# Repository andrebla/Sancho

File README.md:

# Sancho
DIY macro keyboard

|  | 
| - |

Sancho is an open-source custom macro keyboard. An OLED display show keys functions in real time, and an encoder is used to change functions.
 
## PCB ##

|  | 
| - |

## Pictures ##
|  | 
| - |

|  |
| - |

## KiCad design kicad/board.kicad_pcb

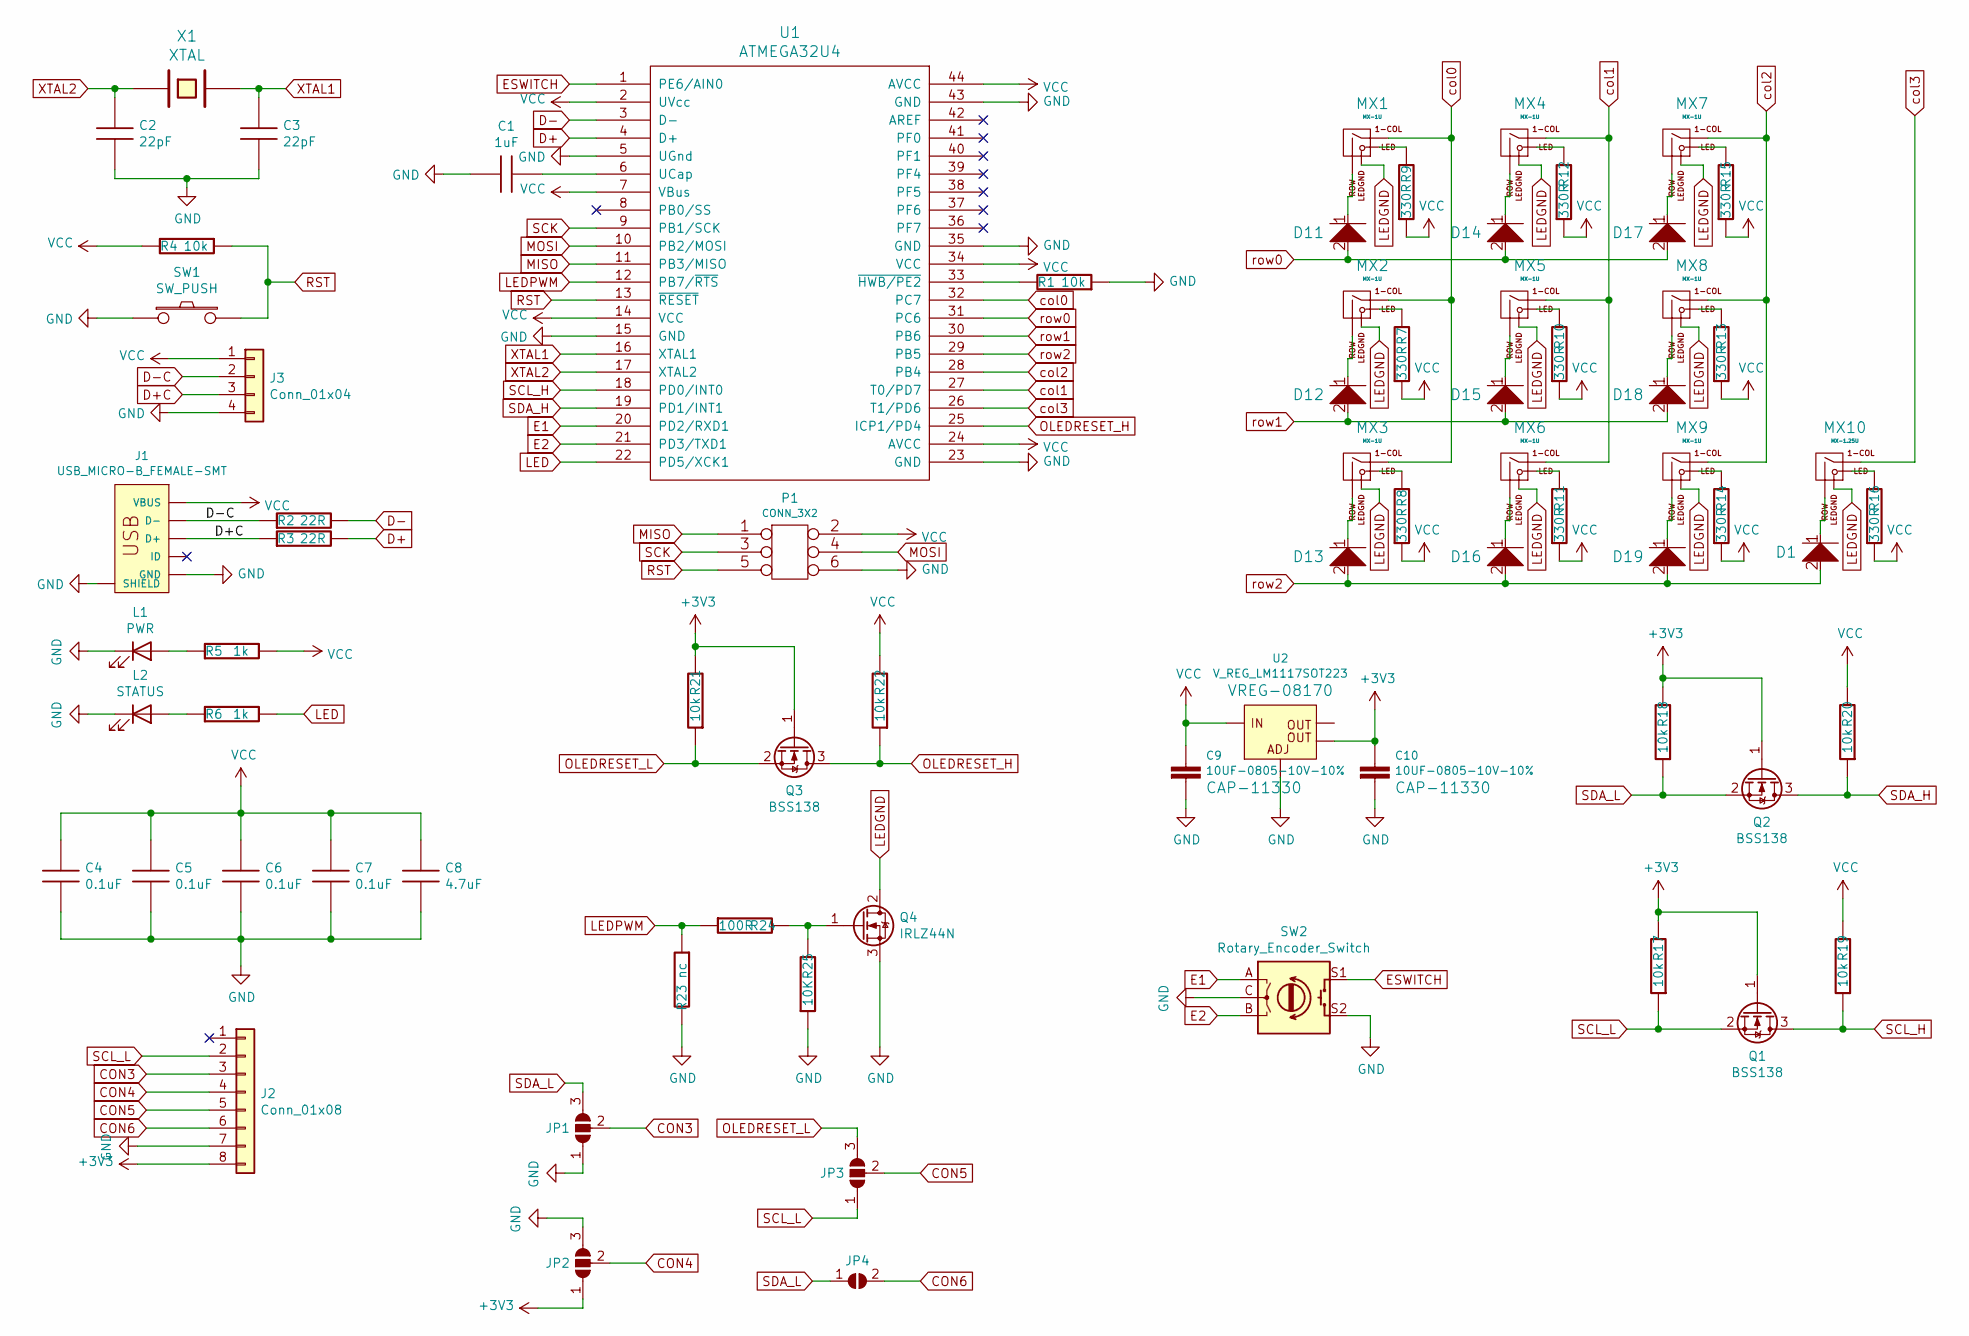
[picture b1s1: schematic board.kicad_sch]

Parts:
C1: 1uF; C_0603_1608Metric
C2, C3: 22pF; C_0603_1608Metric
C4, C5, C6, C7: 0.1uF; C_0603_1608Metric
C8: 4.7uF; C_0603_1608Metric
C9, C10: 10UF-0805-10V-10%; C_0805_2012Metric
D1, D11, D12, D13, D14, D15, D16, D17, D18, D19: D; D_SOD123_axial
J1: USB_MICRO-B_FEMALE-SMT; USB-B-MICRO-SMD
J2: Conn_01x08; PinHeader_1x08_P2.54mm_Vertical
J3: Conn_01x04; 1X04_1.27MM
JP1, JP2, JP3: SolderJumper_3_Open; SolderJumper-3_P1.3mm_Open_RoundedPad1.0x1.5mm
JP4: SolderJumper_2_Open; SolderJumper-2_P1.3mm_Open_RoundedPad1.0x1.5mm
L1: PWR; LED_0603_1608Metric
L2: STATUS; LED_0603_1608Metric
MX1, MX2, MX3, MX4, MX5, MX6, MX7, MX8, MX9: MX-1U
MX10: MX-1.25U
P1: CONN_3X2; AVR_ICSP_3x2
Q1, Q2, Q3: BSS138; SOT-23
Q4: IRLZ44N; SOT-223-3_TabPin2
R1, R4, R17, R18, R19, R20, R21, R22: 10k; R_0603_1608Metric
R2, R3: 22R; R_0603_1608Metric
R5, R6: 1k; R_0603_1608Metric
R7, R8, R9, R10, R11, R12, R13, R14, R15, R16: 330R; R_0603_1608Metric
R23: nc; R_0603_1608Metric
R24: 100R; R_0603_1608Metric
R25: 10K; R_0603_1608Metric
SW1: SW_PUSH; SW_SPST_FSMSM
SW2: Rotary_Encoder_Switch; RotaryEncoder_Alps_EC11E-Switch_Vertical_H20mm
U1: ATMEGA32U4; QFP44
U2: V_REG_LM1117SOT223; SOT223
X1: XTAL; Crystal_SMD_HC49-SD

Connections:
+3V3: C10.1, J2.8, JP2.1 (A), Q1.1 (G), Q2.1 (G), Q3.1 (G), R17.2, R18.2, R21.2, U2.4 (OUT)
CON3: J2.3, JP1.2 (C)
CON4: J2.4, JP2.2 (C)
CON5: J2.5, JP3.2 (C)
CON6: J2.6, JP4.2 (B)
D+: R3.2, U1.4 (D+)
D+C: J1.D+, J3.3, R3.1
D-: R2.2, U1.3 (D-)
D-C: J1.D-, J3.2, R2.1
E1: SW2.A, U1.20 (PD2/RXD1)
E2: SW2.B, U1.21 (PD3/TXD1)
ESWITCH: SW2.S1, U1.1 (PE6/AIN0)
GND: C1.1, C2.2, C3.2, C4.2, C5.2, C6.2, C7.2, C8.2, C9.2, C10.2, J1.GND, J1.SHIE (SHIELD), J2.7, J3.4, JP1.1 (A), JP2.3 (B), L1.1 (K), L2.1 (K), P1.6, Q4.3 (S), R1.1, R23.2, R25.1, SW1.1, SW2.C, SW2.S2, U1.5 (UGnd), U1.15 (GND), U1.23 (GND), U1.35 (GND), U1.43 (GND), U2.1 (ADJ)
LED: R6.2, U1.22 (PD5/XCK1)
LEDGND: MX1.4 (LEDGND), MX2.4 (LEDGND), MX3.4 (LEDGND), MX4.4 (LEDGND), MX5.4 (LEDGND), MX6.4 (LEDGND), MX7.4 (LEDGND), MX8.4 (LEDGND), MX9.4 (LEDGND), MX10.4 (LEDGND), Q4.2 (D)
LEDPWM: R23.1, R24.1, U1.12 (PB7/~RTS)
MISO: P1.1, U1.11 (PB3/MISO)
MOSI: P1.4, U1.10 (PB2/MOSI)
unnamed: C1.2, U1.6 (UCap)
unnamed: D1.1, MX10.2 (ROW)
unnamed: D11.1, MX1.2 (ROW)
unnamed: D12.1, MX2.2 (ROW)
unnamed: D13.1, MX3.2 (ROW)
unnamed: D14.1, MX4.2 (ROW)
unnamed: D15.1, MX5.2 (ROW)
unnamed: D16.1, MX6.2 (ROW)
unnamed: D17.1, MX7.2 (ROW)
unnamed: D18.1, MX8.2 (ROW)
unnamed: D19.1, MX9.2 (ROW)
unnamed: L1.2 (A), R5.1
unnamed: L2.2 (A), R6.1
unnamed: MX1.3 (LED), R9.2
unnamed: MX2.3 (LED), R7.2
unnamed: MX3.3 (LED), R8.2
unnamed: MX4.3 (LED), R12.2
unnamed: MX5.3 (LED), R10.2
unnamed: MX6.3 (LED), R11.2
unnamed: MX7.3 (LED), R15.2
unnamed: MX8.3 (LED), R13.2
unnamed: MX9.3 (LED), R14.2
unnamed: MX10.3 (LED), R16.2
unnamed: Q4.1 (G), R24.2, R25.2
unnamed: R1.2, U1.33 (~HWB/PE2)
OLEDRESET_H: Q3.3 (D), R22.1, U1.25 (ICP1/PD4)
OLEDRESET_L: JP3.3 (B), Q3.2 (S), R21.1
RST: P1.5, R4.1, SW1.2, U1.13 (~RESET)
SCK: P1.3, U1.9 (PB1/SCK)
SCL_H: Q1.3 (D), R19.1, U1.18 (PD0/INT0)
SCL_L: J2.2, JP3.1 (A), Q1.2 (S), R17.1
SDA_H: Q2.3 (D), R20.1, U1.19 (PD1/INT1)
SDA_L: JP1.3 (B), JP4.1 (A), Q2.2 (S), R18.1
VCC: C4.1, C5.1, C6.1, C7.1, C8.1, C9.1, J1.VBUS, J3.1, P1.2, R4.2, R5.2, R7.1, R8.1, R9.1, R10.1, R11.1, R12.1, R13.1, R14.1, R15.1, R16.1, R19.2, R20.2, R22.2, U1.2 (UVcc), U1.7 (VBus), U1.14 (VCC), U1.24 (AVCC), U1.34 (VCC), U1.44 (AVCC), U2.3 (IN)
XTAL1: C3.1, U1.16 (XTAL1), X1.2
XTAL2: C2.1, U1.17 (XTAL2), X1.1
col0: MX1.1 (COL), MX2.1 (COL), MX3.1 (COL), U1.32 (PC7)
col1: MX4.1 (COL), MX5.1 (COL), MX6.1 (COL), U1.27 (T0/PD7)
col2: MX7.1 (COL), MX8.1 (COL), MX9.1 (COL), U1.28 (PB4)
col3: MX10.1 (COL), U1.26 (T1/PD6)
row0: D11.2, D14.2, D17.2, U1.31 (PC6)
row1: D12.2, D15.2, D18.2, U1.30 (PB6)
row2: D1.2, D13.2, D16.2, D19.2, U1.29 (PB5)

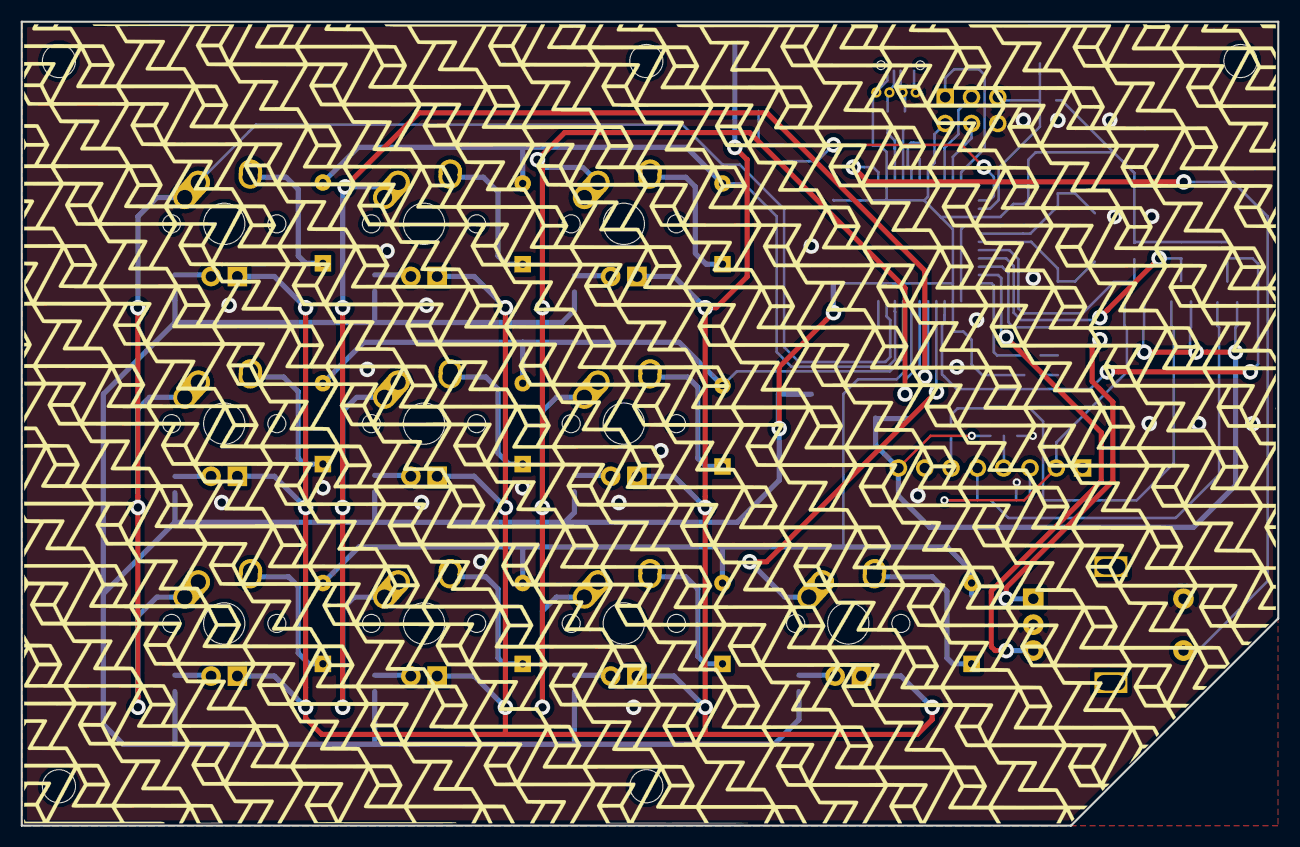
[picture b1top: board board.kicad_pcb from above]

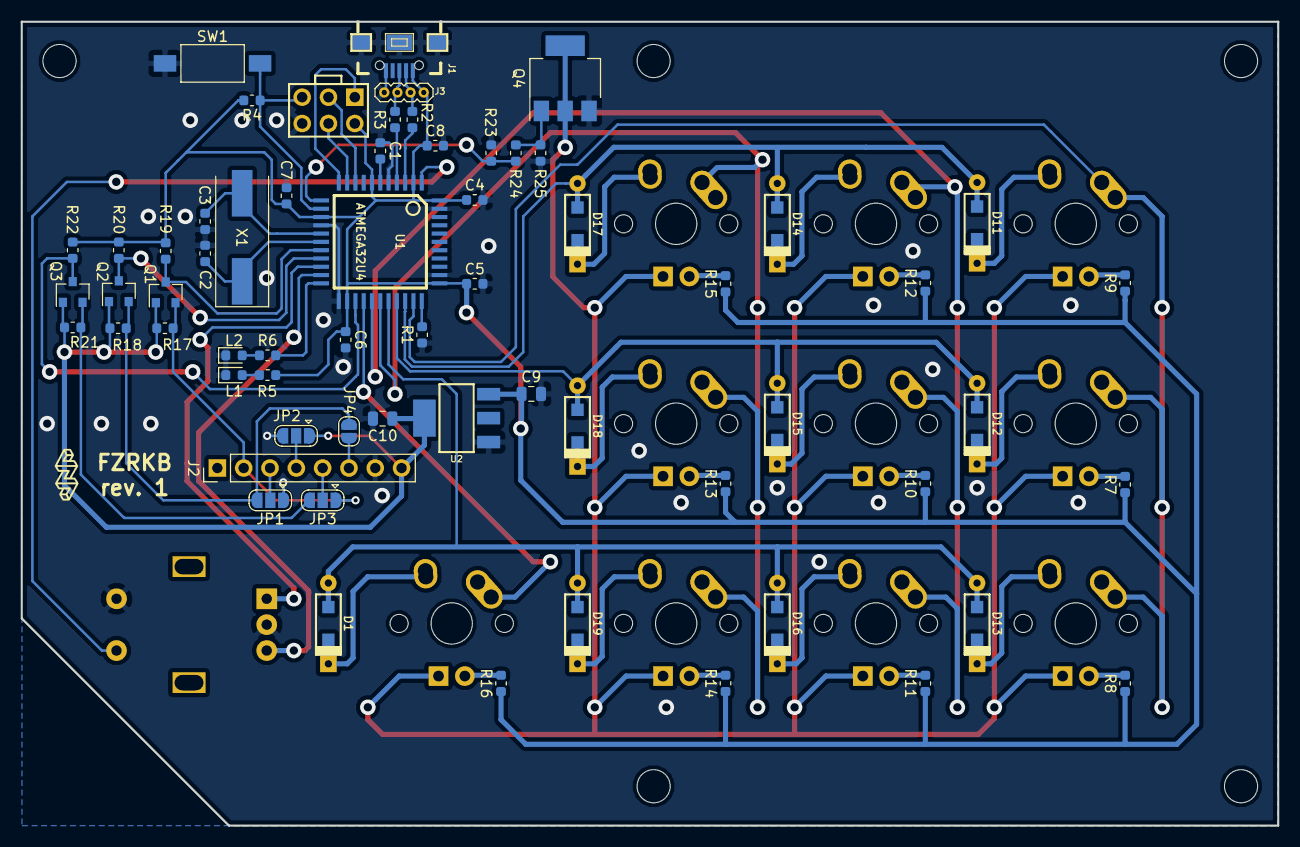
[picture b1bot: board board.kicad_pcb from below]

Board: 2 copper layers, 121.3 x 77.6 mm, 74 parts (63 on the bottom side), 61 nets.
